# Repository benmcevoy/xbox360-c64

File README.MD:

# XBOX 360 Controller to C64

Try and get a USB 360 controller to work on the c64

xinput support is from https://github.com/Ryzee119/tusb_xinput

DPAD and Right analog stick can be used as joystick.

A is fire.

B is up/jump.

X and Y are autofire.

So far I can read (refer: device.h):

- xbox 360 wireless controller :)
- xbox 360 wired controller 
- generic wired switch controller 
- ps4 ds4
- GP2040-CE ps4, xinput, arcade, gp2040, directinput
- various mice, but as there is no DAC not much we can do with it... yet.  I would like to emulate a CBM 1351.

I cannot read but have on hand to test with:

- GP2040-CE ps3 
- GP2040-CE nintendo 
- real ps3
- 8bitdo ultimate

TODO:

- DONE: read controller via tinyusb
- DONE: dpad is joystick
- DONE: A is fire
- DONE: B is UP
- DONE: Analog stick map to d-pad, with a threshold
- NOPE: Web interface to configure? see the pico fight stick
- NOPE: Analog stick is POTX/POTY - yeah maybe not - got no DAC
- NOPE: X and Y are c64gs secondary fire? - this I can do
- DONE: PS4 controller? yep
- DONE: read controller via tinyusb

Things I wish I had done/done differently...

- connect all C64 pins to GPIO, for the POTX/Y as second buttons 
- use an USB header instead of the pico usb port (as it is a pain and needs an adapter)
- use the waveshare pico or a "stamp" board (it's a lot smaller)
- use the PCB manufacturer to add the transistors and resistors as SMD parts
- and basically get the size down and remove the need for USB A to micro adapter
- analog support, either a digital pot or DAC
- better use of the LED for status
- some way to configure it? not much to configure, but it would be nice.

## prepare

clone with submodules, e,g,

`git clone --recurse-submodules git://github.com/benmcevoy/xbox360-c64`

or you may need to run the below under the pico-sdk folder.

```
cd pico-sdk
git submodule init 
git submodule update
```

export environment variables 
- i use .envrc https://direnv.net/
- or use  ~/.bashrc 
- or whatever

`export PICO_SDK_PATH=/path/to/xbox360-c64/pico-sdk`

## cmake
```
cd ./src/build
# debug build
cmake ../ -DCMAKE_BUILD_TYPE=Debug
```

## make

or use `./build.sh`

```
cd src/build/x360c64
make -j4
```

## build and deploy

```
# make executable
chmod +x ./build.sh
chmod +x ./deploy.sh
chmod +x ./monitor.sh
```

```
# get the picoprobe uf2 https://github.com/raspberrypi/picoprobe
# build, then deploy via picoprobe, then start monitoring UART

./build.sh && ./deploy.sh && ./monitor.sh
```

# Schematic

For USB HID power the Pico via VBUS and not VSYS. VBUS needs power so it can power the controllers.

USB controller is plugged directly into the Pico USB port.  

Thanks to this, https://www.hackster.io/DocSnyderde/connect-usb-joystick-to-commodore-c64-2fb5ba

In the current v02 design power is taken direct from the C64 control port. This mean the USB controller is also being powered from the C64. 

Do not plug in the adapter while the power is on.

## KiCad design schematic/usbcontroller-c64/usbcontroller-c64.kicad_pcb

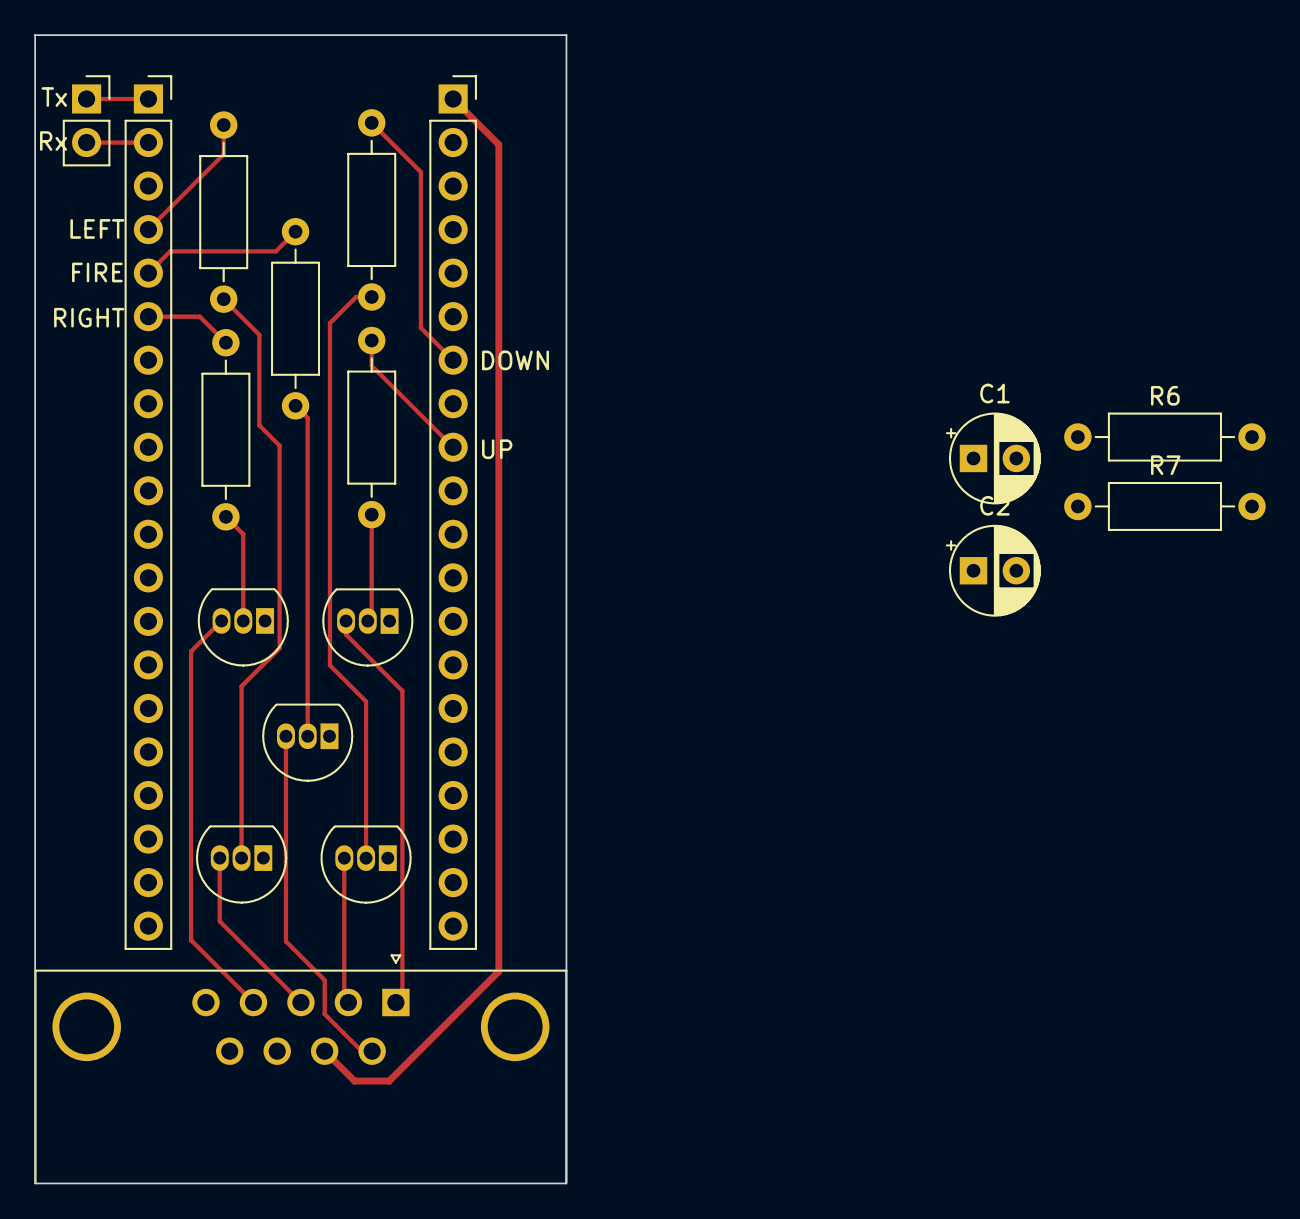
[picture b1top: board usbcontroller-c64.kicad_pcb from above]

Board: 2 copper layers, 31.0 x 67.0 mm, 18 parts (0 on the bottom side), 20 nets.

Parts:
C1, C2: 39pF; CP_Radial_D5.0mm_P2.50mm
J1, J2: Conn_01x20_Socket; PinSocket_1x20_P2.54mm_Vertical
J5: Conn_01x02_Socket; PinSocket_1x02_P2.54mm_Vertical
J6: DE9_Receptacle; DSUB-9_Female_Horizontal_P2.77x2.84mm_EdgePinOffset7.70mm_H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
Q1, Q2, Q3, Q4, Q5: PN2222A; TO-92_Inline
R1, R2, R3, R4, R5: 22K; R_Axial_DIN0207_L6.3mm_D2.5mm_P10.16mm_Horizontal
R6, R7: 1K; R_Axial_DIN0207_L6.3mm_D2.5mm_P10.16mm_Horizontal

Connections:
/DOWN: J6.2, Q4.3 (C)
/FIRE: J6.6, Q2.3 (C)
/LEFT: J6.3, Q1.3 (C)
/LOW_POTAX: C2.1, R7.2
/LOW_POTAY: C1.1, R6.2
/RIGHT: J6.4, Q3.3 (C)
/RX: J1.2, J5.2
/TX: J1.1, J5.1
/UP: J6.1, Q5.3 (C)
GND: C1.2, C2.2, J2.3, J6.8, Q1.1 (E), Q2.1 (E), Q3.1 (E), Q4.1 (E), Q5.1 (E)
unnamed: J1.4, R1.1
unnamed: J1.5, R2.1
unnamed: J1.6, R3.1
unnamed: J2.7, R4.1
unnamed: J2.9, R5.1
unnamed: Q1.2 (B), R1.2
unnamed: Q2.2 (B), R2.2
unnamed: Q3.2 (B), R3.2
unnamed: Q4.2 (B), R4.2
unnamed: Q5.2 (B), R5.2

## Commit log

2023-10-14 init
2023-10-14 cleanup readme
2023-10-14 state the project goal
2023-10-14 messing up the submodule
2023-10-14 update module to develop branch hopefully
2023-10-14 stablise
2023-10-14 get the basic host example to work
2023-10-14 strip back to just HID
2023-10-14 well works with ps4.
2023-10-15 read cheap/fake nintendo controller
2023-10-15 start to tidy up concerns
2023-10-15 normalize data struct a bit
2023-10-15 controller can now send state to gpio
2023-10-19 GPIO is simpler when using a transistor
2023-10-22 attempt to make a pcb
2023-10-22 show the right image
2023-10-22 add tx/rx for debug
2023-10-22 generate drill files
2023-10-22 zip up for manufacture
2023-10-22 align GPIO pins to expected inputs
2023-10-22 another attempt to make xbobx controller work, but fail
2023-10-28 xinput
2023-10-28 fork pico-sdk so i can make changes
2023-10-28 remove submodule, tryign to move to a fork:
2023-10-28 submodule madness
2023-10-28 diff
2023-10-28 fix up modules
2023-10-29 xbox support
2023-10-29 map buttons to xbox style ABXY
2023-10-29 tweaking up xbox controller
2023-11-03 xbox analog is 16 bit signed
2023-11-03 left right were mixed up
2023-11-05 waiting on some crimp things for final test but this basically v1
2023-11-07 autofire on X
2023-11-07 autofire on Y
2023-11-26 update schematic to usb db9 connector and power
2023-12-14 version 2, autofire, direct power
2024-02-25 xbox 360 wireless
2024-02-25 turn off debug
2024-02-25 update readme - can read wireless
2024-02-25 update the uf2 for wireless xbox support
2024-02-27 tidy up
2024-02-27 tidy
2024-02-27 update readme with ideas
2024-03-01 blink LED in a useful way
2024-05-27 start sketching out mouse support
2024-09-18 remove forked pico-sdk depeancy and get back on the normal one
2024-09-19 can now use PIO for USB - currently turned off until I make a PCB
2024-09-19 update release uf2 to latest
2024-09-19 tweak flashing lights for wireless 360
2024-09-20 fix autofire
2024-10-13 remove broken release
2024-10-13 tweak for my open ce controller
